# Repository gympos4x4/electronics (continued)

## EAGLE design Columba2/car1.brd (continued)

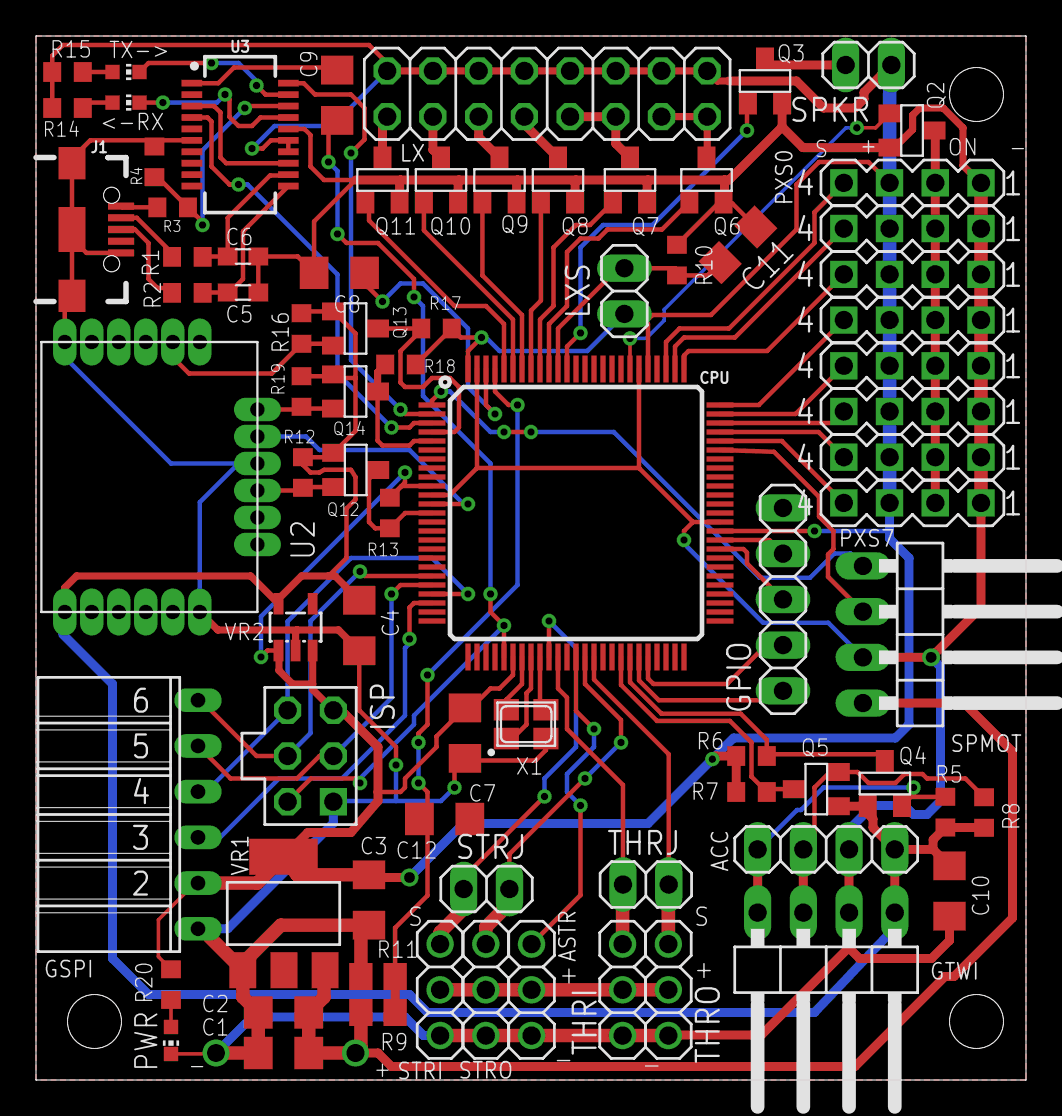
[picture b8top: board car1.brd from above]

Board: 2 copper layers, 55.0 x 58.0 mm, 79 parts (0 on the bottom side), 76 nets.

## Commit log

2018-05-27 Submit EDA data
2018-05-27 Added brd
2018-12-20 Much change such wow
    Added VCU V4R1
    Added PMC 1 & 2
    Added interrupter sensor
    Added proximity sensor V2
2019-01-13 PMC revision (V2.1)
2019-01-25 electronics update (post NF2019)
2019-03-31 WIP VCU V5
2019-04-02 VCU V5 WIP 2
2019-04-02 VCU V5.0 (Final)
